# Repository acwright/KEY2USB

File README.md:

KEY2USB
=======

A non-invasive **Commodore 64** expansion port cartridge that lets the machine's own physical keyboard act as a **USB HID keyboard** for a connected PC running the VICE emulator. Plug it in, power on the C64, connect a USB cable — no case modification, no soldering into the keyboard.

---

## Table of Contents

- [Overview](#overview)
- [Compatibility](#compatibility)
- [Quick Start](#quick-start)
- [Architecture](#architecture)
- [Mode Jumper](#mode-jumper)
- [Hardware](#hardware)
  - [KEY2USB Board](#key2usb-board)
    - [Revision History](#revision-history)
- [Firmware](#firmware)
- [VICE Setup](#vice-setup)
  - [Joysticks](#joysticks)
  - [RESTORE](#restore)
  - [Verifying your setup](#verifying-your-setup)
  - [x128 (C128 native mode)](#x128-c128-native-mode)
  - [VIC-20 (xvic)](#vic-20-xvic)
- [Software](#software)
- [CAD](#cad)
- [Production](#production)
- [Schematics](#schematics)
- [Libraries](#libraries)
- [Bill of Materials](#bill-of-materials)
- [Purchase](#purchase)
- [License](#license)

---

## Overview

**KEY2USB** is a C64 cartridge that solves a specific problem: when running the VICE emulator on a PC alongside a real Commodore 64, you can't easily use the C64's authentic keyboard as a USB input device without modifying the machine. KEY2USB plugs into the expansion port and bridges the C64's keyboard matrix — read by the C64's own 6502 — to a USB HID keyboard interface, using no invasive hardware modifications.

Nothing inside the machine is touched. The cartridge takes over the C64 on power-up, scans the keyboard matrix itself, and reports every make/break to the PC as a standard USB HID boot keyboard. Power comes from the expansion port; the only cable is USB.

## Compatibility

| Machine | Supported | Notes |
|---------|-----------|-------|
| **Commodore 64** (all revisions) | Yes | Primary target |
| **Commodore 64C** | Yes | Identical keyboard matrix |
| **Commodore 128 / 128D** | Yes | Runs in C64 mode — see below. Verified on real hardware |
| **Ultimate 64** | Yes | Verified on real hardware |

On a **C128**, the cartridge asserts `/EXROM`, which the C128 detects at reset and
uses to boot straight into C64 mode — so KEY2USB comes up on its own with no key
combination needed. Every key the C128 shares with the C64 works normally; the
C128's extra keys (numeric keypad, ESC, TAB, ALT, HELP, LINE FEED, NO SCROLL, the
separate cursor pad, CAPS LOCK and 40/80 DISPLAY) are not reported in C64 mode.

For the **full C128 keyboard** in VICE's `x128`, move the [mode jumper](#mode-jumper)
to C128: the cartridge then runs in native C128 mode and reports all 91 keys. See
[x128](#x128-c128-native-mode).

If a particular C128 does not autostart, power on while holding the **C=** key to
force C64 mode.

## Quick Start

1. With the C64 **powered off**, insert KEY2USB into the expansion port.
2. Connect the USB cable to your PC. The device enumerates as a standard HID
   keyboard — no drivers needed.
3. Power on the C64. The `KEY2USB` splash screen appears; the cartridge has taken
   over the machine and is scanning the keyboard.
4. In VICE, set **Settings → Keyboard → Keyboard Mapping → Positional**. This step
   is mandatory — see [VICE Setup](#vice-setup).
5. Type on the C64. Keystrokes arrive at the PC.

While KEY2USB is running, the C64 is dedicated to being a keyboard — it does not
return to BASIC. Power off and remove the cartridge to use the machine normally.

## Architecture

- **ROM side**: A 28C64 EEPROM holds two 4K firmware banks. The bank and `/EXROM` state are selected together by a single `MODE` jumper, set to **C64** on shipping units — see [Mode Jumper](#mode-jumper).
- **Glue logic**: A 74LS32 (quad OR gate) generates a write strobe from `/IO1` + `R/W`; a 74LS273 (8-bit D flip-flop register) latches the key-event byte the 6502 firmware writes to `$DE00`; a 74LS74 (dual D flip-flop) provides a single `RDY` handshake flag.
- **USB side**: An ATmega328P-PU runs the [V-USB](https://www.obdev.at/products/vusb/index.html) software USB stack, polls the latch via the `RDY` flag, and sends 8-byte USB HID boot-protocol keyboard reports. A 16 MHz crystal clocks the MCU.
- **USB front end**: Two 68Ω series resistors on D+ and D−, two 1N5227B (3.6V) Zener diodes to clamp the lines to spec, and a 1.5kΩ D− pull-up to +5V to signal a low-speed USB device — no 3.3V rail needed.
- **PCB constraint**: 100% through-hole / DIP — no SMD parts.

The two sides share only a single byte-wide latch and one ready flag — no shared clock or bus timing requirements.

## Mode Jumper

The board carries a 3-pin `MODE` header (J1) that selects the EEPROM bank and the
`/EXROM` state together:

| Jumper position | EEPROM bank | `/EXROM` | Behavior |
|-----------------|-------------|----------|----------|
| **C64** (GND) — *factory default* | Lower 4K | Asserted | Autostarts via the `CBM80` signature. On a C128, forces a boot into C64 mode. |
| **C128** (+5V) | Upper 4K | Released | Autostarts as a C128 external function ROM in native mode. |

**Assembled cartridges ship with the jumper set to C64 and the case closed over
it.** The C64 bank is the supported configuration; it covers the C64, C64C, Ultimate 64, 
and the C128 by way of C64 mode. There is no need to change it, and the case has no opening for it.

The C128 bank is for C128 owners who want the **whole C128 keyboard** in `x128`:
the 8×8 matrix plus the numeric keypad, ESC, TAB, ALT, HELP, LINE FEED, NO SCROLL,
the cursor pad, CAPS LOCK and 40/80 DISPLAY. It is verified on a real C128 (every
key, in `x128` too). It has no use on a C64. Changing the jumper means opening the
case, and is entirely at your own discretion.

## Hardware

This repository contains the KiCad 10.0 PCB design for the KEY2USB board.

### KEY2USB Board
`Hardware/`

A single cartridge PCB hosting the ROM, glue logic, and USB MCU. Provides:

- **ROM**: 28C64 EEPROM (DIP-28) preloaded with the keyboard-scan firmware
- **Write strobe**: 74LS32 quad OR gate — asserts `WRSTB` from `/IO1` + `R/W`
- **Key-event latch**: 74LS273 octal D flip-flop register — captures the byte written to `$DE00`
- **Handshake flag**: 74LS74 dual D flip-flop — one half as the `RDY`/`/CLRRDY` flag
- **USB MCU**: ATmega328P-PU (DIP-28) running V-USB, reads the latch, emits USB HID reports
- **Crystal**: 16 MHz THT crystal + 2× 20pF load capacitors
- **USB front end**: USB Type B connector, 68Ω series resistors, 1N5227B Zener clamps, 1.5kΩ D− pull-up
- **Mode select**: 3-pin 2.54mm jumper header — set to C64 at the factory (GND, asserts `/EXROM`, lower 4K EEPROM bank); see [Mode Jumper](#mode-jumper)
- **Bus connection**: 44-pin C64 expansion port edge connector
- **Power**: Drawn from the C64's own +5V via the expansion port

#### Revision History

**Rev 1.0**

- Initial release.

## Firmware

Both firmwares are implemented in `Firmware/` (see `Firmware/README.md` for build,
flash, and layout details). Set VICE's keyboard mapping to **Positional** — see
[VICE Setup](#vice-setup).

**6502 side (C64 bank — the shipping configuration):**
- Autostart via the `CBM80` signature, take over the machine, and draw a centered `KEY2USB` splash on the 40-column screen.
- Scan the 8×8 keyboard matrix directly via CIA #1 (`$DC00`/`$DC01`) for raw make/break events and modifier state — no KERNAL buffer.
- Scan **both joystick ports** on the same CIA #1 ports (they share the matrix lines, so no extra hardware is involved).
- On any key or joystick state change, write a one-byte event to `$DE00`.
- Report RESTORE (an NMI, not a matrix key) as its own event.
- While nothing is held, send a SYNC event about once a second so the ATmega
  can release anything it still believes is down.

The upper bank holds the C128 native-mode firmware, which autostarts from a
`CBM` / `$01` external function ROM header. It scans the 8×8 matrix, the three extra
key columns via `$D02F`, and the CAPS LOCK and 40/80 DISPLAY latches, and tells the
ATmega to use `x128`'s host keys. See `Firmware/Cart/README.md`.

**ATmega328/328P side:**
- Poll `RDY`; on set, read the key byte from `PINC`/`PINB`, pulse `/CLRRDY`.
- Run V-USB (low-speed USB 1.1); translate to USB HID usages and send an 8-byte boot-protocol keyboard report (each one twice, since V-USB cannot re-send a report the host missed).
- Configured as a self-powered USB device.

## VICE Setup

One setting trips people up every time, so set it before anything else:

- **Keyboard mapping must be Positional, not Symbolic.** In VICE:
  **Settings → Keyboard → Keyboard Mapping → Positional**. This is the single
  most common first-time setup mistake — if keys look wrong, check this first.
  The reason is worth understanding, because it explains the whole signal path:

  A USB keyboard never transmits characters. Press `A` and it sends HID usage
  `0x04`; the USB spec names that "Keyboard a and A", but the name is only
  documentation — the code means *"the key where a US keyboard has A"*. Your OS
  decides it is an `A` by applying the selected layout. On AZERTY the same key
  sends the same `0x04` and the OS renders `Q`.

  KEY2USB is positional end to end for exactly that reason. The 6502 detects a
  key by matrix position (`col*8 + row`) and never computes a character; the
  ATmega looks that keyID up in `keymap.h` and emits the HID usage for the PC key
  in the corresponding physical spot; VICE's Positional keymap maps PC positions
  back onto C64 matrix positions. Positions in, positions through, positions out
  — nothing resolves to a character until VICE finally does it.

  Symbolic breaks that chain by inserting a translation. Press **SHIFT + 2**,
  which is `"` on a C64. The cartridge sends shift plus the position code for
  `2`; the host applies its US layout and concludes you typed `@`. Symbolic then
  asks "which C64 key produces `@`?" and presses that one — wrong. Positional
  ignores the character entirely, sees "physical shift + physical 2", and gives
  you the `"` you actually pressed. The keystroke arrived correctly either way;
  Symbolic just did an unwanted extra translation using a PC layout that does
  not match a C64's.
- USB HID reports are sent as a standard boot-protocol keyboard — no special
  VICE driver or configuration is needed beyond the keymap.

### Joysticks

Both joystick ports are scanned by the cartridge and arrive at the host as
**ordinary keystrokes**, so VICE has to be told which keys mean "joystick".
Everything lives on the numeric keypad, split so the two ports cannot collide.

First tick **Settings → Joystick → Allow keyset joysticks**. Without it VICE
ignores both the Numpad device and keysets, and the stick just types keypad
keys. VICE keeps this setting separately for each emulator (`x64sc`, `x128` …),
so set it in each one you use.

**Port 2** — the easy one, nothing else to configure:

> **Settings → Joystick → Joystick Port #2 → Numpad** (called *Keypad* in some
> VICE versions)

VICE's built-in Numpad device already maps keypad digits (`8/2/4/6` for
directions, `7/9/1/3` for diagonals, `0`/`5` for fire), and the cartridge's
port-2 mapping was chosen to match it exactly.

**Port 1** — needs a keyset, because Numpad can only serve one port:

> **Settings → Joystick → Joystick Port #1 → Keyset A**, then
> **Configure Keyset A**:

| Direction | Key |
|-----------|-----|
| North | Keypad **−** |
| South | Keypad **+** |
| West  | Keypad **/** |
| East  | Keypad **&ast;** |
| Fire  | Keypad **enter** |

Port 1 uses keypad *symbols* rather than digits or function keys for two
reasons: the digits are already claimed by the Numpad device serving port 2,
and VICE's positional keymap binds F12 to RESTORE, so a function-key keyset
cannot use it. The symbols are untouched by both.

### RESTORE

RESTORE is not part of the keyboard matrix (it pulls the C64's NMI line), but
the cartridge reports each press anyway, as **Page Up** — the key VICE's
positional keymap uses for RESTORE. RUN/STOP + RESTORE works in the emulator
with no configuration.

### A caveat worth knowing

A held joystick direction grounds a line in the keyboard matrix, so it also
**phantom-presses real keys** — exactly as it does on a real C64. This is
inherent to the wiring, not a firmware choice, and it is left in place so the
cartridge behaves like the bare machine.

It hits **port 1** hardest: a held direction grounds a matrix *row*, pressing
all 8 keys in it — which includes RETURN, INST/DEL and CLR/HOME. Expect stray
keystrokes while a port-1 direction is held. **Port 2 is the one to use in
practice**; it grounds a column instead, which only aliases if you are also
pressing a key in that same column.

### Verifying your setup

`Software/key2usbtest.prg` shows live joystick state for both ports plus the
last keys received, so you can confirm the cartridge and your VICE
configuration in one place. On a Mac, `Software/key2usbmon` checks the
cartridge itself with VICE out of the picture: it reads the raw USB reports and
names the C64 key behind each one. See [Software/](Software/).

### `x128` (C128 native mode)

With the [mode jumper](#mode-jumper) on **C128**, the cartridge runs in native C128
mode and the ATmega switches to the host keys VICE's `x128` positional keymap
expects. Use **Settings → Keyboard → Keyboard Mapping → Positional** here too.

| C128 key | Host key | | C128 key | Host key |
|----------|----------|-|----------|----------|
| F1 / F3 / F5 / F7 | F1 / F2 / F3 / F4 | | ESC | F9 |
| HELP | F5 | | TAB | F10 |
| LINE FEED | F6 | | ALT | F11 |
| 40/80 DISPLAY | F7 (tap) | | CAPS LOCK | F12 (tap) |
| NO SCROLL | F8 | | Numeric keypad | Keypad |
| Cursor pad | Arrow keys | | RESTORE | Page Up |

Three things behave differently from C64 mode:

- **The keypad is the C128 keypad, and also the port-2 joystick.** They share host
  keys, so choose per session: for the joystick, set **Joystick Port #2 → Numpad**
  (or *Keypad*) with **Allow keyset joysticks** ticked, and the C128 keypad then
  moves the stick too; to type on the keypad, set **Joystick Port #2 → None**.
- **CRSR keys.** In native mode `x128` drives only the separate cursor pad from the
  host arrows, and SHIFT does not reverse it. The cartridge therefore sends the
  main CRSR keys as Right/Down, or Left/Up while SHIFT is held, so they move the
  cursor exactly as on the real machine.
- **CAPS LOCK and 40/80 DISPLAY latch mechanically**, while `x128` toggles them on
  each host key press. Each movement of the latch is sent as one tap, so `x128`
  follows the real key. If they ever disagree, toggle the key twice. 40/80 only
  takes effect at reset, as on the real machine.

`Software/key2usbmon --c128 --check` checks all 89 keys from the host side, and
`Software/key2usbtest128.prg` (BASIC 7.0, run inside `x128`) names each key `x128`
sees, plus the CAPS LOCK and 40/80 state.

### VIC-20 (`xvic`)

The cartridge also drives VICE's VIC-20 emulator, with the same **Positional**
setting and no keymap changes. This works because VICE's two positional keymaps
are the same map in different coordinates — `VIC20/gtk3_pos.vkm` states the
relationship outright:

    # to convert from C64 to VIC20:
    # change rows 7 -> 0, 0 -> 7
    # change columns 7 -> 3, 3 -> 7

Applying that permutation and diffing the two files (VICE 3.x, GTK3, US layout)
gives:

| | |
|---|---|
| Host keysyms in each map | 151 / 151 |
| Present in one but not the other | 0 |
| Agree under the permutation | 150 |
| Differ | 1 |

The lone difference is cosmetic: `>` sits at matrix position `5 4` in both, but
carries shiftflag `1` on the C64 ("combined with shift") and `8` on the VIC-20
("can be shifted or not"). The cartridge sends the physical `.` key and physical
SHIFT as separate events, so both yield `>` regardless. The RESTORE entries
(`Page_Up` / `F12` / `Prior`) and all twenty joyport keypad entries are identical.

Both emulators therefore consume the same host keys and route them to the
same-labelled machine keys. `keymap.h` is built as the inverse of the C64
positional map, which makes it equally the inverse of the VIC-20 one.

Two caveats:

- This was established by comparing the shipped keymap files, not by a hardware
  session on `xvic`. The mapping is confirmed; end-to-end behaviour is not.
- **The VIC-20 has only one control port.** Point the cartridge's port-2 mapping
  (the keypad digits, via the Numpad device) at it; the port-1 keyset has nothing
  to connect to.

## Software
`Software/`

Host-side test software:

- `key2usbmon` (macOS) reads the cartridge's raw USB reports directly, with no
  emulator involved, and names the C64 key behind each one. `--check` runs a
  press-every-key checklist. Build with `make key2usbmon` (requires `swiftc`
  from the Xcode Command Line Tools).
- `key2usbtest.prg` runs inside VICE and shows live joystick state for both
  ports plus the last keystrokes received, so you can verify your VICE
  configuration. Build with `make key2usbtest.prg` (requires `petcat`, which
  ships with VICE) or use the prebuilt `.prg`.
- `key2usbtest128.prg` is the BASIC 7.0 equivalent for `x128` in C128 mode (mode
  jumper on C128). It names every C128 key `x128` sees, including the keypad and
  the other extra keys, plus the CAPS LOCK and 40/80 state.

See [Software/README.md](Software/README.md).

## CAD
`CAD/`

3D models and render images for the KEY2USB board.

## Production
`Production/`

JLCPCB-ready fabrication files, BOM, and component positions for PCB fabrication.

## Schematics
`Schematics/`

PDF schematic for the KEY2USB board.

## Libraries
`Libraries/`

Custom KiCad symbol and footprint libraries, including the C64 expansion port edge connector footprint and the USB Type B connector footprint.

## Bill of Materials

| Reference | Qty | Value | Description | Digikey |
|-----------|-----|-------|-------------|---------|
| C1, C2, C3, C4 | 4 | 100nF | Ceramic disc capacitor — IC bypass | [478-5732-ND](https://www.digikey.com/en/products/filter?keywords=478-5732-ND) |
| C5, C6 | 2 | 20pF | Ceramic disc capacitor — crystal load | [478-7724-ND](https://www.digikey.com/en/products/filter?keywords=478-7724-ND) |
| D1, D2 | 2 | 1N5227B | 3.6V Zener diode, DO-35 — USB line clamp | [1N5227B-ND](https://www.digikey.com/en/products/filter?keywords=1N5227B-ND) |
| J1 | 1 | MODE | 3-pin 2.54mm header + jumper cap — mode select, factory-set to C64 | [S1121EC-03-ND](https://www.digikey.com/en/products/filter?keywords=S1121EC-03-ND) |
| J2 | 1 | C64 EXP PORT | C64 expansion port edge connector (44-pin, 3.96mm pitch) | |
| J3 | 1 | USB | USB Type B connector, through-hole (UJ2-BH-BL1-TH) | [102-5886-ND](https://www.digikey.com/en/products/filter?keywords=102-5886-ND) |
| R1, R2 | 2 | 68Ω | Resistor, 1/4W — USB D+ / D− series | [S68CACT-ND](https://www.digikey.com/en/products/filter?keywords=S68CACT-ND) |
| R3 | 1 | 1.5kΩ | Resistor, 1/4W — USB D− pull-up to +5V | [S1.5KCACT-ND](https://www.digikey.com/en/products/filter?keywords=S1.5KCACT-ND) |
| U1 | 1 | 28C64 | 8K×8 EEPROM, DIP-28 — holds C64 and C128 firmware banks | [AT28C64B-15PU-ND](https://www.digikey.com/en/products/filter?keywords=AT28C64B-15PU-ND) |
| U2 | 1 | 74LS32 | Quad 2-input OR gate, DIP-14 — generates write strobe | [296-1658-5-ND](https://www.digikey.com/en/products/filter?keywords=296-1658-5-ND) |
| U3 | 1 | 74LS273 | 8-bit D flip-flop register, DIP-20 — key-event latch | [296-1657-5-ND](https://www.digikey.com/en/products/filter?keywords=296-1657-5-ND) |
| U4 | 1 | 74LS74 | Dual D flip-flop, DIP-14 — RDY handshake flag | [296-1668-5-ND](https://www.digikey.com/en/products/filter?keywords=296-1668-5-ND) |
| U5 | 1 | ATmega328P-PU | 8-bit AVR MCU, DIP-28 — V-USB and HID firmware | [ATMEGA328-PU-ND](https://www.digikey.com/en/products/filter?keywords=ATMEGA328-PU-ND) |
| Y1 | 1 | 16 MHz | Crystal, through-hole — ATmega328P clock | [3155-16M20P2/49US-ND](https://www.digikey.com/en/products/filter?keywords=3155-16M20P2/49US-ND) |

## Purchase

KEY2USB is available as a kit on Tindie for those who would rather not order
boards from a fab and source parts themselves.

## License

Hardware designs are released under the [CERN Open Hardware Licence Version 2 – Permissive](https://ohwr.org/cern_ohl_p_v2.txt).

The cartridge ROM firmware (`Firmware/Cart/`) and the controller firmware's own
sources (`Firmware/Controller/src/`, `include/`) are MIT-licensed. The controller
firmware links the vendored [V-USB](https://www.obdev.at/vusb/) driver, which is
GPL v2/v3, so the built controller firmware image is distributed under the GPL;
this repository is its corresponding source.

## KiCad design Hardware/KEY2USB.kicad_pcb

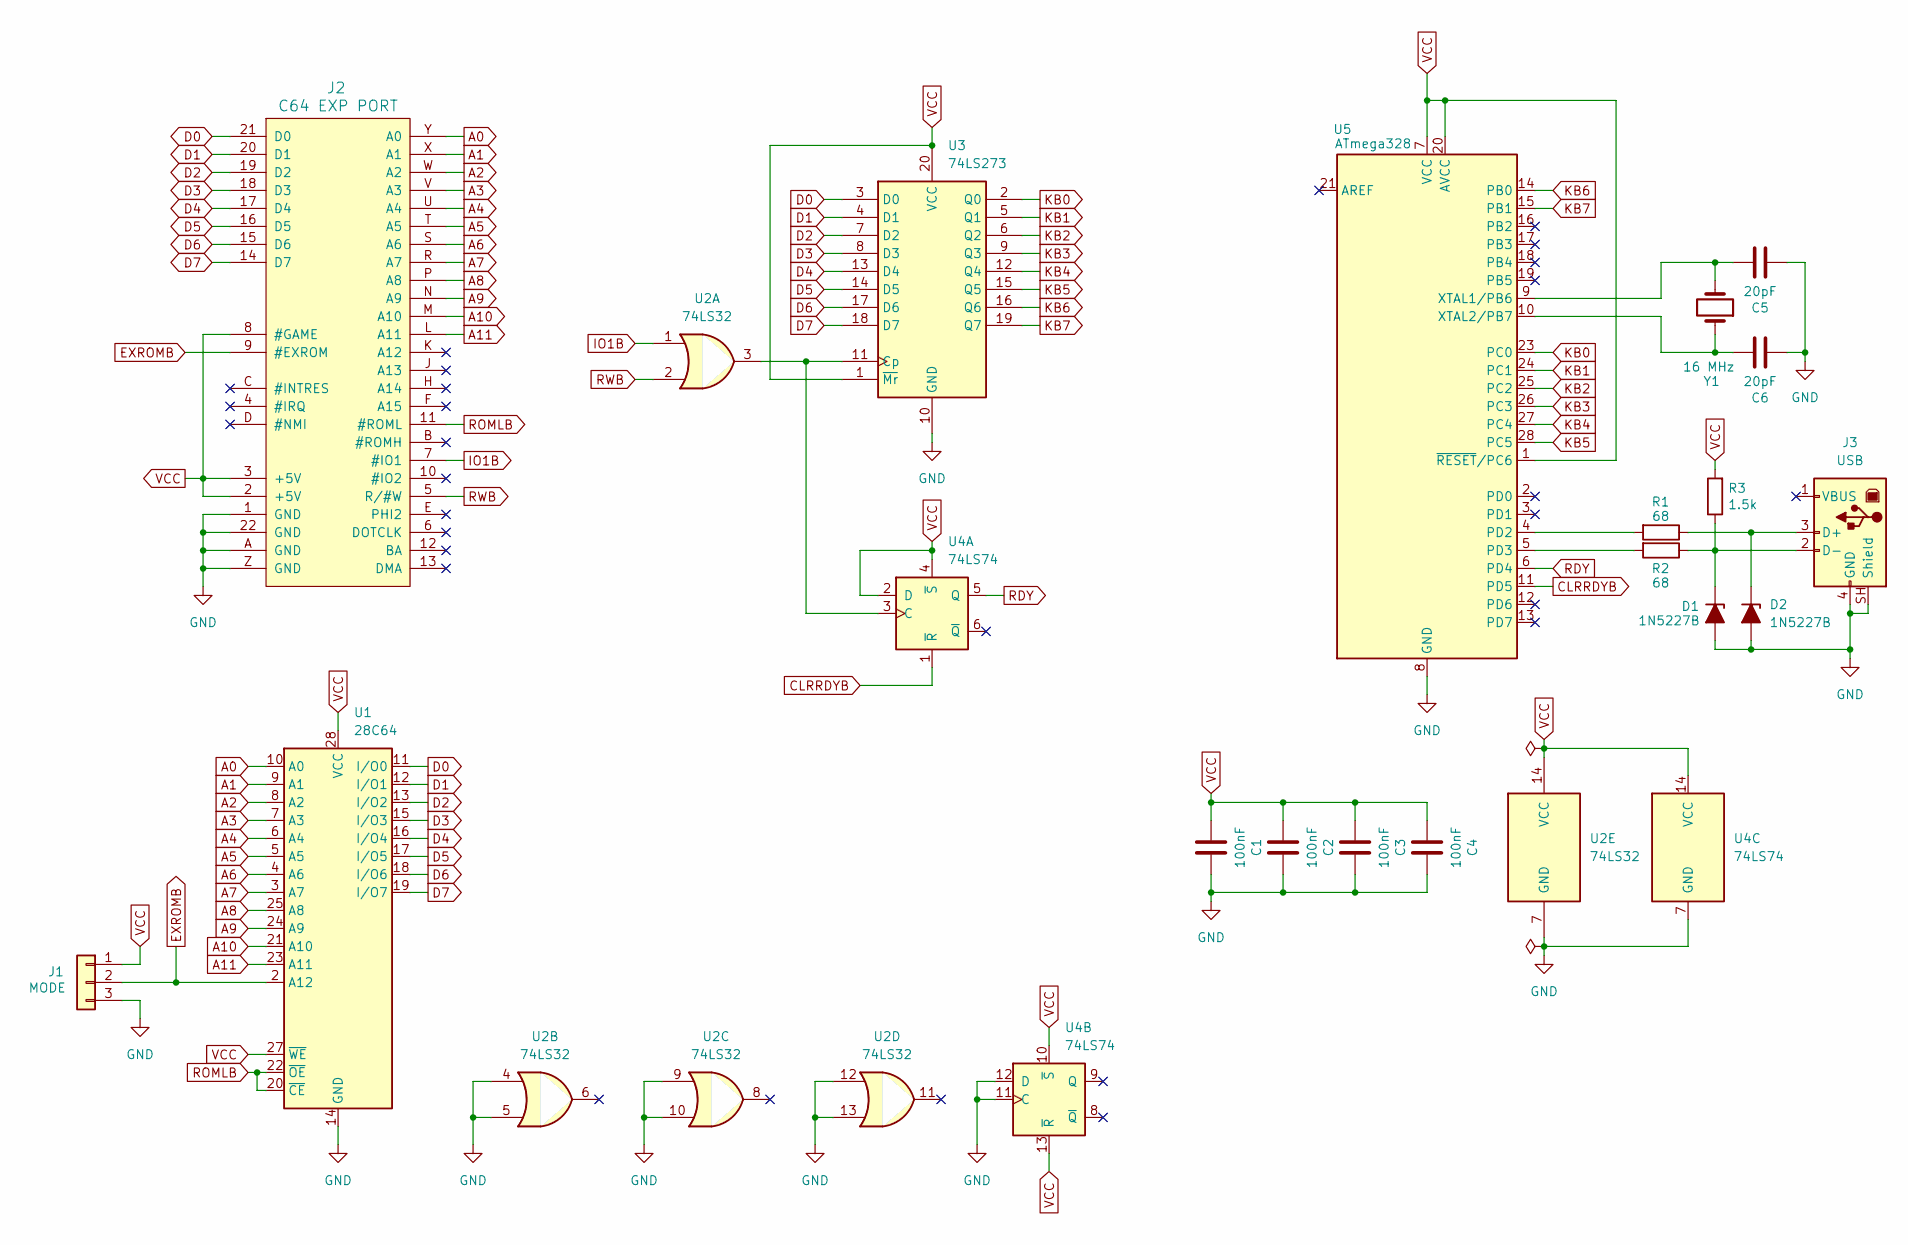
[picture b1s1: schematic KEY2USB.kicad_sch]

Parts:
C1, C2, C3, C4: 100nF; C_Disc_D5.0mm_W2.5mm_P2.50mm; Digikey 478-5732-ND
C5, C6: 20pF; C_Disc_D5.0mm_W2.5mm_P2.50mm; Digikey 478-7724-ND
D1, D2: 1N5227B; D_DO-35_SOD27_P10.16mm_Horizontal; Digikey 1N5227B-ND
J1: MODE; PinHeader_1x03_P2.54mm_Horizontal; Digikey S1121EC-03-ND
J2: C64 EXP PORT; C64_EXPANSION_PORT
J3: USB; UJ2-BH-BL1-TH; Digikey 102-5886-ND
R1, R2: 68; R_Axial_DIN0207_L6.3mm_D2.5mm_P10.16mm_Horizontal; Digikey S68CACT-ND
R3: 1.5k; R_Axial_DIN0207_L6.3mm_D2.5mm_P10.16mm_Horizontal; Digikey S1.5KCACT-ND
U1: 28C64; DIP-28_W15.24mm_Socket_LongPads; Digikey AT28C64B-15PU-ND
U2: 74LS32; DIP-14_W7.62mm_Socket_LongPads; Digikey 296-1658-5-ND
U3: 74LS273; DIP-20_W7.62mm_Socket_LongPads; Digikey 296-1657-5-ND
U4: 74LS74; DIP-14_W7.62mm_Socket_LongPads; Digikey 296-1668-5-ND
U5: ATmega328; DIP-28_W7.62mm_Socket_LongPads; Digikey ATMEGA328-PU-ND
Y1: 16 MHz; Crystal_HC49-U_Vertical; Digikey 3155-16M20P2/49US-ND

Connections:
A0: J2.Y (A0), U1.10 (A0)
A1: J2.X (A1), U1.9 (A1)
A2: J2.W (A2), U1.8 (A2)
A3: J2.V (A3), U1.7 (A3)
A4: J2.U (A4), U1.6 (A4)
A5: J2.T (A5), U1.5 (A5)
A6: J2.S (A6), U1.4 (A6)
A7: J2.R (A7), U1.3 (A7)
A8: J2.P (A8), U1.25 (A8)
A9: J2.N (A9), U1.24 (A9)
A10: J2.M (A10), U1.21 (A10)
A11: J2.L (A11), U1.23 (A11)
CLRRDYB: U4.1 (~R), U5.11 (PD5)
D0: J2.21 (D0), U1.11 (I/O0), U3.3 (D0)
D1: J2.20 (D1), U1.12 (I/O1), U3.4 (D1)
D2: J2.19 (D2), U1.13 (I/O2), U3.7 (D2)
D3: J2.18 (D3), U1.15 (I/O3), U3.8 (D3)
D4: J2.17 (D4), U1.16 (I/O4), U3.13 (D4)
D5: J2.16 (D5), U1.17 (I/O5), U3.14 (D5)
D6: J2.15 (D6), U1.18 (I/O6), U3.17 (D6)
D7: J2.14 (D7), U1.19 (I/O7), U3.18 (D7)
EXROMB: J1.2, J2.9 (#EXROM), U1.2 (A12)
GND: C1.2, C2.2, C3.2, C4.2, C5.2, C6.2, D1.2 (A), D2.2 (A), J1.3, J2.1 (GND), J2.22 (GND), J2.A (GND), J2.Z (GND), J3.4 (GND), J3.SH (Shield), U1.14 (GND), U2.4, U2.5, U2.7 (GND), U2.9, U2.10, U2.12, U2.13, U3.10 (GND), U4.7 (GND), U4.11 (C), U4.12 (D), U5.8 (GND), U5.22 (GND)
IO1B: J2.7 (#IO1), U2.1
KB0: U3.2 (Q0), U5.23 (PC0)
KB1: U3.5 (Q1), U5.24 (PC1)
KB2: U3.6 (Q2), U5.25 (PC2)
KB3: U3.9 (Q3), U5.26 (PC3)
KB4: U3.12 (Q4), U5.27 (PC4)
KB5: U3.15 (Q5), U5.28 (PC5)
KB6: U3.16 (Q6), U5.14 (PB0)
KB7: U3.19 (Q7), U5.15 (PB1)
unnamed: D1.1 (K), J3.2 (D-), R2.1, R3.1
unnamed: D2.1 (K), J3.3 (D+), R1.1
unnamed: U2.3, U3.11 (Cp), U4.3 (C)
unnamed: R1.2, U5.4 (PD2)
unnamed: R2.2, U5.5 (PD3)
unnamed: C5.1, U5.9 (XTAL1/PB6), Y1.2
unnamed: C6.1, U5.10 (XTAL2/PB7), Y1.1
RDY: U4.5 (Q), U5.6 (PD4)
ROMLB: J2.11 (#ROML), U1.20 (~CE), U1.22 (~OE)
RWB: J2.5 (R/#W), U2.2
VCC: C1.1, C2.1, C3.1, C4.1, J1.1, J2.2 (+5V), J2.3 (+5V), J2.8 (#GAME), R3.2, U1.27 (~WE), U1.28 (VCC), U2.14 (VCC), U3.1 (~Mr), U3.20 (VCC), U4.2 (D), U4.4 (~S), U4.10 (~S), U4.13 (~R), U4.14 (VCC), U5.1 (~RESET/PC6), U5.7 (VCC), U5.20 (AVCC)

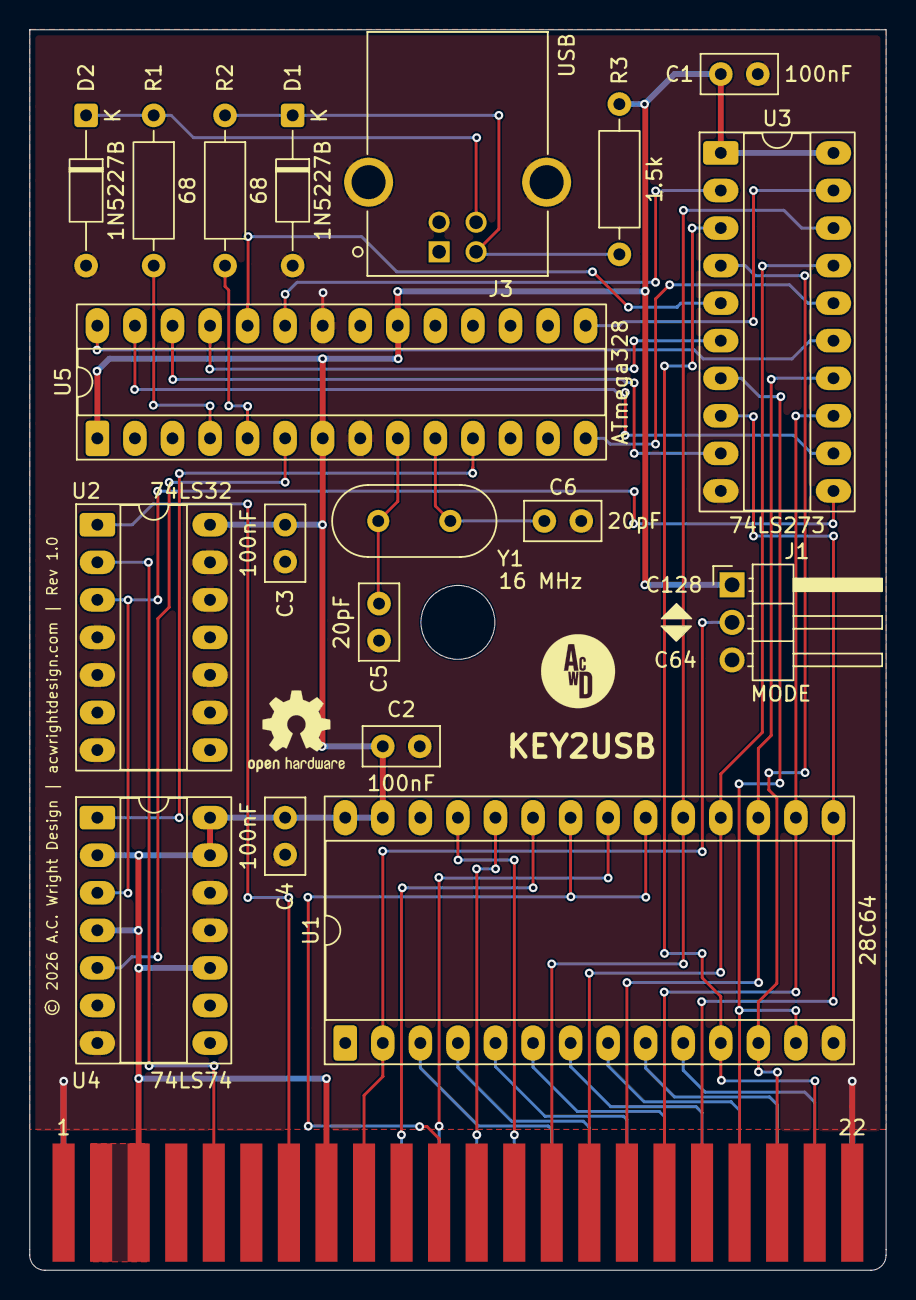
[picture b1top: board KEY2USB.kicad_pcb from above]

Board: 2 copper layers, 57.9 x 83.9 mm, 20 parts (0 on the bottom side), 43 nets.

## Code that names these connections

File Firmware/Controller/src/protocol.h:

/* =============================================================================
 *  protocol.h - KEY2USB event-byte contract (ATmega side)
 * =============================================================================
 *  Mirror of the 6502 side (Firmware/Cart/Cart.inc). One byte is latched into
 *  the 74LS273 each time the 6502 writes to $DE00; the 74LS74 raises RDY.
 *
 *      bit 7      : 1 = key pressed (make), 0 = key released (break)
 *      bits 6..0  : keyID  (C64 matrix = col*8+row, 0..63; C128 ext = 64..;
 *                           joystick port 2 = 112..116, port 1 = 120..124;
 *                           RESTORE = 126)
 *
 *  0x7F (keyID 127, break form) is SYNC: the cartridge holds nothing, so every
 *  key, modifier and stick contact must read as released. It is sent at
 *  power-up/reset and about once a second while idle, so a lost release can
 *  never leave a key stuck on the host.
 *
 *  Pin contract (verified against Hardware/KEY2USB.kicad_sch, U5):
 *      KB0..KB5 -> PC0..PC5      KB6..KB7 -> PB0..PB1
 *      RDY      -> PD4 (input)   /CLRRDY  -> PD5 (output, active low)
 *      USB D+   -> PD2/INT0      USB D-   -> PD3
 */
#ifndef KEY2USB_PROTOCOL_H
#define KEY2USB_PROTOCOL_H

#include <avr/io.h>

#define EV_PRESSED   0x80        /* bit 7 of the event byte */
#define EV_KEYID(b)  ((b) & 0x7F)
#define EV_SYNC      0x7F        /* "nothing held" - see above */

/* SYNC128 (keyID 125, break form): SYNC from the cartridge's C128 bank. It
 * also selects the C128 mappings, because x128 expects the function keys,
 * cursor keys and the extra C128 keys on different host keys than x64 does.
 * Plain SYNC selects the C64 mappings again. */
#define EV_SYNC128   0x7D

/* C128 bank only: CAPS LOCK and 40/80 DISPLAY, latching keys outside the
 * matrix (make = latched down). Extended matrix keys are 64..87. */
#define KEY_CAPS     88
#define KEY_4080     89

#define KEY_CRSR_LR  2           /* C64/C128 matrix CRSR keys */
#define KEY_CRSR_UD  7

/* RESTORE pulls NMI rather than sitting in the matrix, and only on its press
 * edge, so the cartridge reports each press as a ~100 ms make/break tap. */
#define KEY_RESTORE  126

/* Joystick keyIDs (mirror of JOY2_BASE / JOY1_BASE in Cart/Cart.inc).
 * Contacts arrive as ordinary key events; the keymap decides what they type. */
#define JOY2_UP      112
#define JOY2_DOWN    113
#define JOY2_LEFT    114
#define JOY2_RIGHT   115
#define JOY2_FIRE    116
#define JOY1_UP      120
#define JOY1_DOWN    121
#define JOY1_LEFT    122
#define JOY1_RIGHT   123
#define JOY1_FIRE    124

#define RDY_PIN      PD4
#define CLRRDY_PIN   PD5

/* Reassemble the latched key byte from the two input ports. */
static inline uint8_t key2usb_read_latch(void)
{
    return (uint8_t)((PINC & 0x3F) | ((PINB & 0x03) << 6));
}

/* True while the 74LS74 says a fresh event is waiting in the latch. */
static inline uint8_t key2usb_event_ready(void)
{
    return (PIND & (1 << RDY_PIN)) != 0;
}

/* Pulse /CLRRDY low to clear the ready flag after consuming an event. */
static inline void key2usb_clear_ready(void)
{
    PORTD &= ~(1 << CLRRDY_PIN);
    /* 74LS74 async clear needs only nanoseconds; a couple of NOPs suffice. */
    __asm__ __volatile__("nop\n\tnop\n\tnop\n\tnop");
    PORTD |= (1 << CLRRDY_PIN);
}

#endif /* KEY2USB_PROTOCOL_H */

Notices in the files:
Hardware/KEY2USB.kicad_pcb:
© 2026 A.C. Wright Design | acwrightdesign.com | Rev 1.0
